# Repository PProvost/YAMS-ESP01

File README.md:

# YAMS-ESP01
Yet Another Motion Sensor - Uses an ESP01 and a cheap PIR motion sensor, sends activation events via MQTT,
optimized for very low power use. Runs on 3 AA batteries (I use Panasonic Eneloop NiMh cells).

## BOM

* ESP8266-01 Module
* HC-SR501 PIR Motion Detector
* MCP1700-3302E TO92 Voltage Regulator
* Resistors:
  - 220 ohm (x1)
  - 3.3K ohm (x1)
* Capacitors:
  - 1uF ceramic (x2)
  - 100nF ceramic (x1)
* Various pin headers, JST and molex connectors as you see fit
* Battery caddy (aim for > 4V but stay within the limits of the MCP1700-3302E)

## Implementation Notes:

* If you have a Puya-based ESP01 module, you may need to apply this patch to get SPIFFS to write correctly:
  https://github.com/letscontrolit/ESPEasy/blob/mega/patches/puya_v3.patch#L8
* You can force the WifiManager to reset its settings by writing the SPIFFS filesystem with a file called
  `/config.json` with the following contents: `{ "reset_settings": true }`. This file is included in the
  /data directory in this repo.

## Building the circuit

Credits: This circuit used in this design is based on the work described in [Benny de Leeuw's article][1].

IMPORTANT!: This is a 3.3V circuit. The HC-SR501 PIR sensor is 5V, so you either need to maintain two power
voltages or modify the PIR to run on 3.3V.

The circuit is designed to be battery powered, requiring between 3.7V and 6V due to the requirements
of the MCP1700 LDO. This requires some special with your PIR sensor. Most of the cheap ones you will
find expect 5V. See below for more information about modding your PIR sensor for 3V3.

Once I've built a few and ironed out the bugs, I will provide STLs for a case and a link to the PCB
on OSHPark.

Please refer to the schematic PDF and the other files in the schematic/ folder.

### Modding the HC-SR501 PIR Sensor

I wanted to reuse the VCC pin on the PIR sensor to make mounting easier, but also to power the PIR sensor
with the same 3.3VDC the ESP takes. For some of my sensors, I made the following modifications successfully:

* Removed the 3V3 voltage regulator
* Connected the cathode (output) side of the diode to the VOUT pad where the regulator had been connected
* Removed the 1k resistor between the controller IC and the signal pin and shorted the two pads.
* NOTE:This permanently changes the sensor to only take 3.3V, do not power it with 5V after removing the regulator.
  If you don't want to remove the regulator from your sensor, you can still power it with 3.3V following the guide [Modifying Cheap PIR Sensors][3], but you may still need to remove the 1k resistor. I've used this approach too.

## Credits & References

1. [Stable ESP01 Motion Sensor][1]
2. [ESP01 Pin Magic][2]
3. [Modifying Cheap PIR Sensors][3]

## TODO:

* Provide a better HASS discovery message
* Better case design
* Button/switch/jumper to make it stay awake (can help with network debugging; see also the DO_NOT_SLEEP define
  in main.cpp)
* Enable [OTA updating](http://esp8266.github.io/Arduino/versions/2.0.0/doc/ota_updates/ota_updates.html),
* Figure out a reset button so you can reset the configuration without flashing the SPIFFS filesystem
  particularly for updating the config.json file but also maybe the firmware.
* (Optional) front facing LED when motion detected
* (Idea) Photoresistor to prevent triggering unless light levels are low enough

[1]: https://medium.com/@leeuwte/stable-esp01-motion-sensor-for-mqtt-2d81c0b1e317
[2]: http://www.forward.com.au/pfod/ESP8266/GPIOpins/ESP8266_01_pin_magic.html
[3]: https://randomnerdtutorials.com/modifying-cheap-pir-motion-sensor-to-work-at-3-3v/

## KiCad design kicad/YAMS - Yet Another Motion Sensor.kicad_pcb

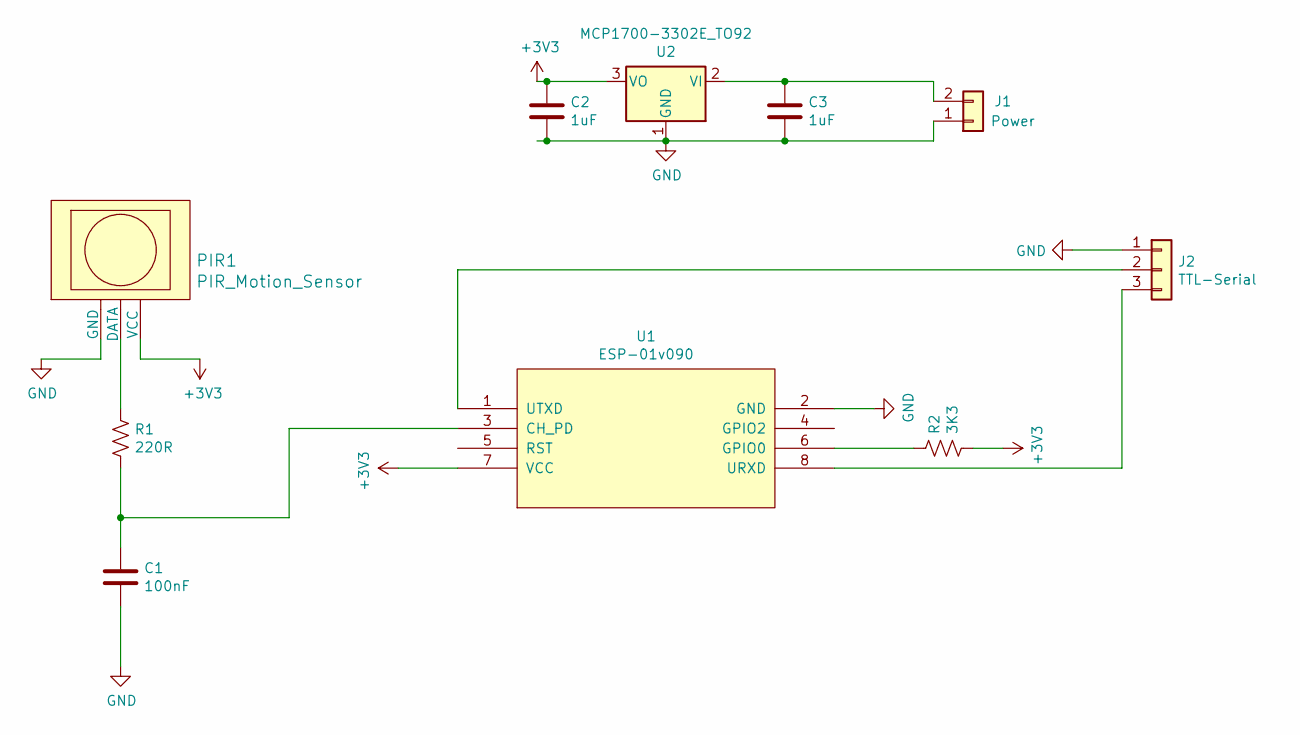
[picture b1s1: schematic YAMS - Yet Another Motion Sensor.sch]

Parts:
C1: 100nF; C_Disc_D3.8mm_W2.6mm_P2.50mm
C2, C3: 1uF; C_Disc_D3.8mm_W2.6mm_P2.50mm
J1: Power; JST_XH_B02B-XH-A_1x02_P2.50mm_Vertical
J2: TTL-Serial; PinHeader_1x03_P2.54mm_Vertical
PIR1: PIR_Motion_Sensor; PIR_Motion_Sensor_Horiz
R1: 220R; R_Axial_DIN0207_L6.3mm_D2.5mm_P7.62mm_Horizontal
R2: 3K3; R_Axial_DIN0207_L6.3mm_D2.5mm_P7.62mm_Horizontal
U1: ESP-01v090; ESP-01
U2: MCP1700-3302E_TO92; TO-92_Inline

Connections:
+3V3: C2.1, PIR1.3 (VCC), R2.2, U1.7 (VCC), U2.3 (VO)
GND: C1.2, C2.2, C3.2, J1.1, J2.1, PIR1.1 (GND), U1.2 (GND), U2.1 (GND)
unnamed: C1.1, R1.2, U1.3 (CH_PD)
unnamed: C3.1, J1.2, U2.2 (VI)
unnamed: J2.2, U1.1 (UTXD)
unnamed: J2.3, U1.8 (URXD)
unnamed: PIR1.2 (DATA), R1.1
unnamed: R2.1, U1.6 (GPIO0)

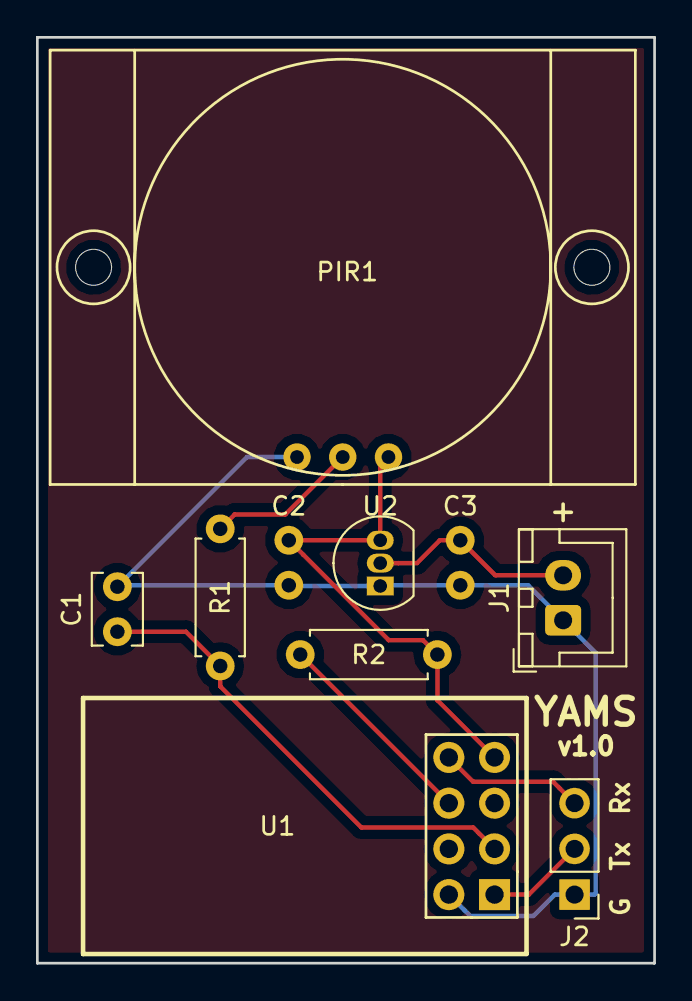
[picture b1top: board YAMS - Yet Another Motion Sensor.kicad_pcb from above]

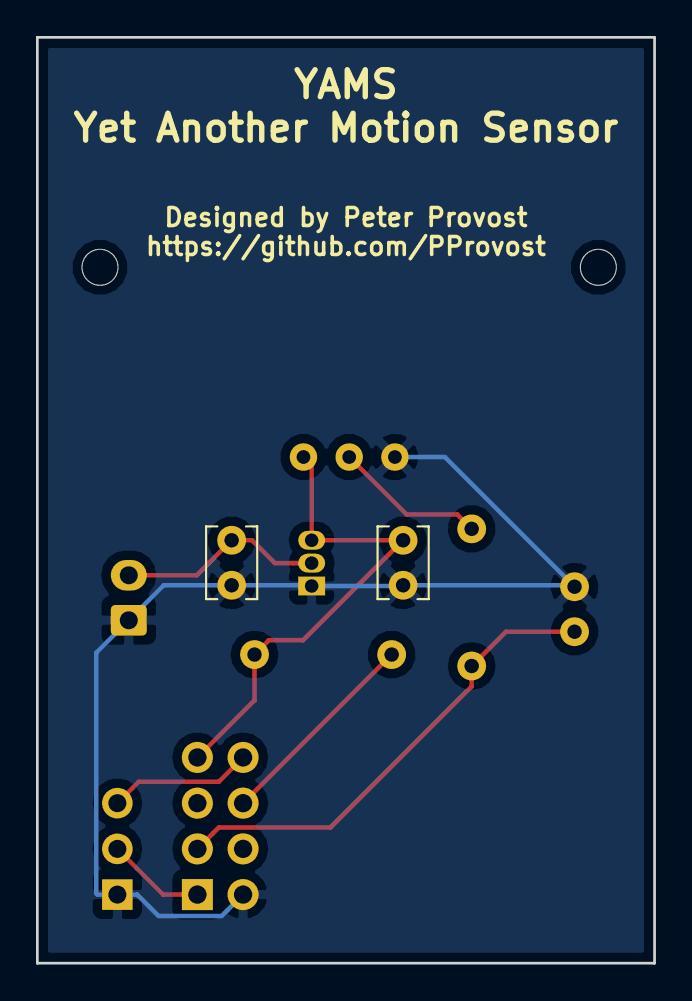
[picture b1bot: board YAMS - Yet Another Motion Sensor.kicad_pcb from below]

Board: 2 copper layers, 34.3 x 51.4 mm, 10 parts (2 on the bottom side), 8 nets.

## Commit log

2019-01-15 Removed static IP for now
2019-01-15 Added KiCad files for circuit and PCB design
2019-01-15 Removed unneeded test folder
2019-01-15 Trying out travisci with ESP builds
2019-01-15 More travis work
2019-01-15 Wrong case in include?
2019-01-16 Still tweaking Travis-CI
2019-01-16 One more time for Travis-CI
2019-01-16 More travis tweaks
2019-01-16 One more time
2019-01-16 Hopefully this works...
2019-01-16 Argh. Why won't Travis pick up the include??
2019-01-16 RTFM!
2019-01-16 Updated readme to show Travis-CI status
2019-01-19 Updates to schematic and PCB
2019-01-19 Initial draft of a 3D printed case
2019-01-19 Report mac address when booting
2019-01-19 Back to DNS with static lease... it is faster
2019-01-19 Added todo list to readme
2019-01-23 Removed vscode intellisense databases (duh!)
2019-01-23 Added WiFiManager configuration
2019-01-23 Readme updates
2019-01-23 One more little thing...
2019-01-23 Updates to readme and few other little things.
2019-01-26 Lots of updates to the case
